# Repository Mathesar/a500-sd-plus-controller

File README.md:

# a500-sd-plus-controller
This is a dual micro-SD card plus Ethernet controller for the Amiga 500.
The controller piggybacks on the odd CIA (CIA A) chip on the Amiga 500 motherboard.

## Table of Contents
* [Micro-SD](#micro-sd)
* [Ethernet](#ethernet)
* [Drivers](#drivers)
* [Performance](#performance)
* [Pictures](#pictures)
* [Building](#building)

## Micro-SD
The two Micro-SD cards are operated in SPI mode.
Using the 68000 movep (move to/from peripheral) instruction and optimized code the driver reaches a raw throughput of up to 450kB/s on a standard 7MHz 68000 CPU. Due to device driver and filesystem overhead the overall speed is lower though.

The primary channel is intended for internal use. The micro-SD card in this slot functions as a fixed harddisk. The secondary channel is intended to be used with an extension cable to hold an external (hot-swappable if the driver supports it) micro-SD card. 
For this purpose, proper measures are taken to control signal integrity over the extension cable. The controller can also handle any current surges that can occur during hot swapping without overloading the Amiga power rail.

## Ethernet
The Ethernet controller is a Microchip ENC28J60 device. It is also connected over SPI and uses the INT2 interrupt. The ENC28J60 supports a 10Mbit network connection.
The interface is built in a slightly non-standard way to maximum immunity for external interference.

## Drivers
The Micro-SD cards are supported by [sd-lide.device](https://github.com/Mathesar/sd_lide.device).

The Ethernet controller is supported by [enc28j60.device](https://github.com/Mathesar/enc28j60.device).

## Performance
On a standard Amiga 500 with a 7MHz 68000 CPU running OS3.1 and AmiTCP 3.0b2 the following performance is reached:

* 250kB/s read speed for the Micro-SD cards as reported by SysInfo.
* Up to 22kB/s network download speed which is mostly limited by CPU speed.

Much better performance which is only limited by the speed of the E-clk (~600..700kB/s) can be expected when a faster CPU is installed.

## Pictures

Proof that this was actually built:

And the obligatory SysInfo screenshot:

## Building
Under [releases](https://github.com/Mathesar/a500-sd-plus-controller/releases) you will find the latest gerbers, bill of materials, bitstream, etc.
The files are in a format that is suitable for most well-known PCBA manufacturers.
I would recommend having the boards soldered professionally. This project uses small compononents and especially the CPLD is not solderable by hand. I had the boards made with all the SMD parts and the ethernet connector mounted. I only soldered the pinheaders and the CIA socket myself. For the pinheaders that plug into the CIA socket on the A500 motherboard, be sure to use the THIN and ROUND (aka "turned") pinheaders. Otherwise the motherboard socket WILL be damaged.

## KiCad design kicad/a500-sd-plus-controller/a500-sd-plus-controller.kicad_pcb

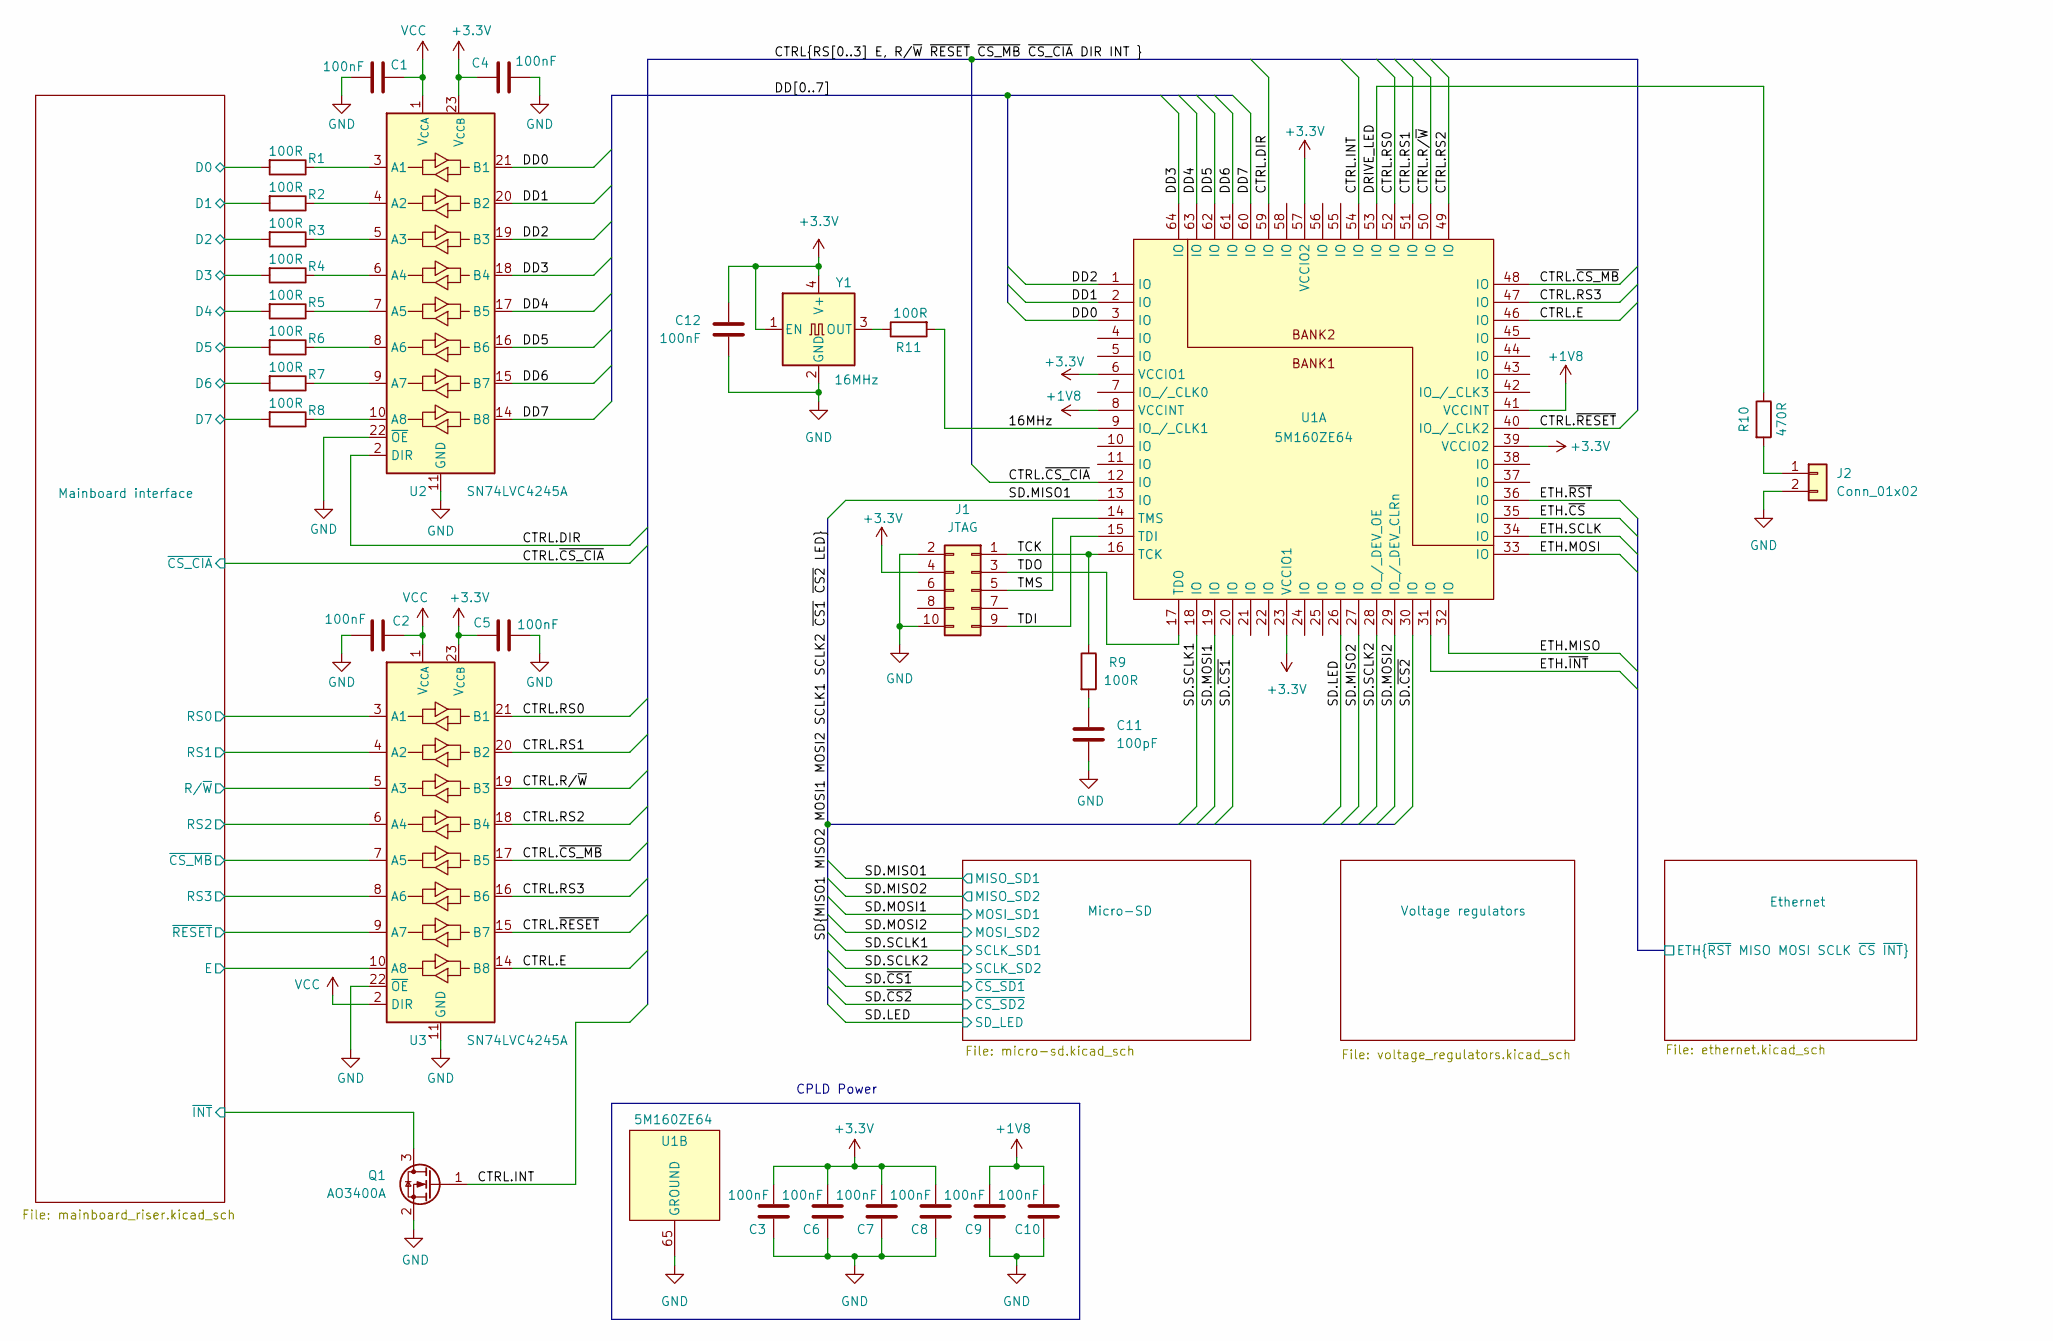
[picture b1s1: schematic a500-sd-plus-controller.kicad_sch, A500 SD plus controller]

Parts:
C1, C2, C3, C4, C5, C6, C7, C8, C9, C10, C12: 100nF; C_0603_1608Metric; LCSC Part # C14663
C11: 100pF; C_0603_1608Metric; LCSC Part # C14858
J1: JTAG; PinHeader_2x05_P2.54mm_Vertical
J2: Conn_01x02; PinHeader_1x02_P2.54mm_Vertical
Q1: AO3400A; SOT-23; MPN AO3400A; LCSC Part # C20917
R1, R2, R3, R4, R5, R6, R7, R8, R9, R11: 100R; R_0603_1608Metric; LCSC Part # C22775
R10: 470R; R_0603_1608Metric; LCSC Part # C23179
U1: 5M160ZE64; EQFP-64_7x7mm_P0.4mm; MPN 5M160ZE64C5N; LCSC Part # C431489
U2, U3: SN74LVC4245A; TSSOP-24_4.4x7.8mm_P0.65mm; MPN SN74LVC4245APWR; LCSC Part # C7859
Y1: 16MHz; Oscillator_SMD_SeikoEpson_SG210-4Pin_2.5x2.0mm; MPN X1G0041710027; LCSC Part # C255993

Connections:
+1V8: C9.1, C10.1, U1.8 (VCCINT), U1.41 (VCCINT); also elsewhere on the board
+3.3V: C3.1, C4.2, C5.2, C6.1, C7.1, C8.1, C12.2, J1.4, U1.6 (VCCIO1), U1.23 (VCCIO1), U1.39 (VCCIO2), U1.57 (VCCIO2), U2.23 (V_{CCB}), U2.24 (V_{CCB}), U3.23 (V_{CCB}), U3.24 (V_{CCB}), Y1.1 (EN), Y1.4 (V+); also elsewhere on the board
/16MHz: R11.2, U1.9 (IO_/_CLK1)
/CTRL.DIR: U1.59 (IO), U2.2 (DIR)
/CTRL.E: U1.46 (IO), U3.14 (B8)
/CTRL.INT: Q1.1 (G), U1.54 (IO)
/CTRL.RS0: U1.52 (IO), U3.21 (B1)
/CTRL.RS1: U1.51 (IO), U3.20 (B2)
/CTRL.RS2: U1.49 (IO), U3.18 (B4)
/CTRL.RS3: U1.47 (IO), U3.16 (B6)
/CTRL.R/~W: U1.50 (IO), U3.19 (B3)
/CTRL.~CS_CIA: U1.12 (IO); also elsewhere on the board
/CTRL.~CS_MB: U1.48 (IO), U3.17 (B5)
/CTRL.~RESET: U1.40 (IO_/_CLK2), U3.15 (B7)
/DD0: U1.3 (IO), U2.21 (B1)
/DD1: U1.2 (IO), U2.20 (B2)
/DD2: U1.1 (IO), U2.19 (B3)
/DD3: U1.64 (IO), U2.18 (B4)
/DD4: U1.63 (IO), U2.17 (B5)
/DD5: U1.62 (IO), U2.16 (B6)
/DD6: U1.61 (IO), U2.15 (B7)
/DD7: U1.60 (IO), U2.14 (B8)
/DRIVE_LED: R10.1, U1.53 (IO)
/Ethernet/ETH.MISO: U1.32 (IO); also elsewhere on the board
/Ethernet/ETH.MOSI: U1.33 (IO); also elsewhere on the board
/Ethernet/ETH.SCLK: U1.34 (IO); also elsewhere on the board
/Ethernet/ETH.~CS: U1.35 (IO); also elsewhere on the board
/Ethernet/ETH.~INT: U1.31 (IO); also elsewhere on the board
/Ethernet/ETH.~RST: U1.36 (IO); also elsewhere on the board
/Mainboard interface/D0: R1.2; also elsewhere on the board
/Mainboard interface/D1: R2.2; also elsewhere on the board
/Mainboard interface/D2: R3.2; also elsewhere on the board
/Mainboard interface/D3: R4.2; also elsewhere on the board
/Mainboard interface/D4: R5.2; also elsewhere on the board
/Mainboard interface/D5: R6.2; also elsewhere on the board
/Mainboard interface/D6: R7.2; also elsewhere on the board
/Mainboard interface/D7: R8.2; also elsewhere on the board
/Mainboard interface/E: U3.10 (A8); also elsewhere on the board
/Mainboard interface/RS0: U3.3 (A1); also elsewhere on the board
/Mainboard interface/RS1: U3.4 (A2); also elsewhere on the board
/Mainboard interface/RS2: U3.6 (A4); also elsewhere on the board
/Mainboard interface/RS3: U3.8 (A6); also elsewhere on the board
/Mainboard interface/R/~W: U3.5 (A3); also elsewhere on the board
/Mainboard interface/~CS_MB: U3.7 (A5); also elsewhere on the board
/Mainboard interface/~INT: Q1.3 (D); also elsewhere on the board
/Mainboard interface/~RESET: U3.9 (A7); also elsewhere on the board
/SD.LED: U1.26 (IO); also elsewhere on the board
/SD.MISO1: U1.13 (IO); also elsewhere on the board
/SD.MISO2: U1.27 (IO); also elsewhere on the board
/SD.MOSI1: U1.19 (IO); also elsewhere on the board
/SD.MOSI2: U1.29 (IO_/_DEV_CLRn); also elsewhere on the board
/SD.SCLK1: U1.18 (IO); also elsewhere on the board
/SD.SCLK2: U1.28 (IO_/_DEV_OE); also elsewhere on the board
/SD.~CS1: U1.20 (IO); also elsewhere on the board
/SD.~CS2: U1.30 (IO); also elsewhere on the board
/TCK: J1.1, R9.1, U1.16 (TCK)
/TDI: J1.9, U1.15 (TDI)
/TDO: J1.3, U1.17 (TDO)
/TMS: J1.5, U1.14 (TMS)
GND: C1.1, C2.1, C3.2, C4.1, C5.1, C6.2, C7.2, C8.2, C9.2, C10.2, C11.1, C12.1, J1.2, J1.10, J2.2, Q1.2 (S), U1.65 (GROUND), U2.11 (GND), U2.12 (GND), U2.13 (GND), U2.22 (~OE), U3.11 (GND), U3.12 (GND), U3.13 (GND), U3.22 (~OE), Y1.2 (GND); also elsewhere on the board
unnamed: C11.2, R9.2
unnamed: J2.1, R10.2
unnamed: R1.1, U2.3 (A1)
unnamed: R2.1, U2.4 (A2)
unnamed: R3.1, U2.5 (A3)
unnamed: R4.1, U2.6 (A4)
unnamed: R5.1, U2.7 (A5)
unnamed: R6.1, U2.8 (A6)
unnamed: R7.1, U2.9 (A7)
unnamed: R8.1, U2.10 (A8)
unnamed: R11.1, Y1.3 (OUT)
VCC: C1.2, C2.2, U2.1 (V_{CCA}), U3.1 (V_{CCA}), U3.2 (DIR); also elsewhere on the board

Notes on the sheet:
CPLD Power

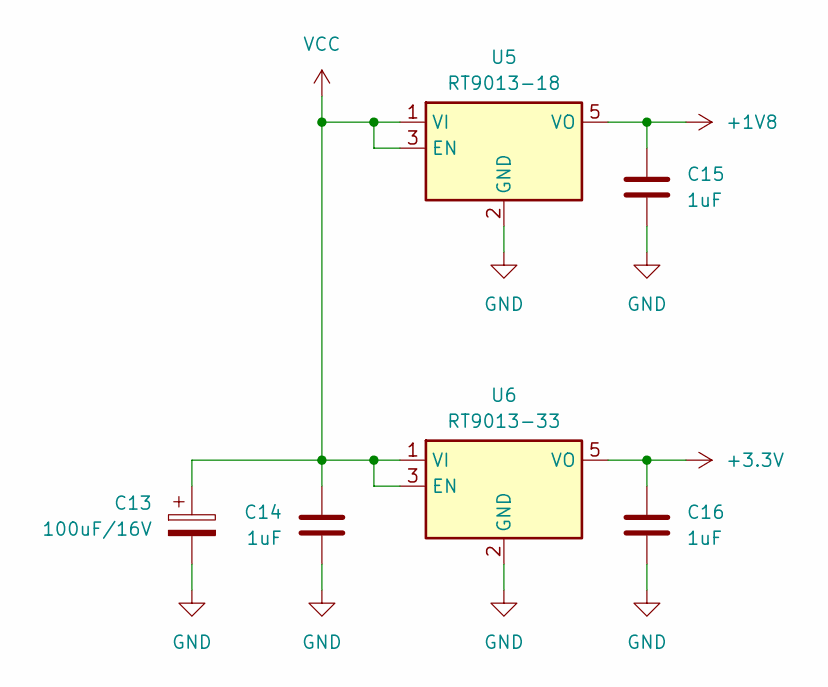
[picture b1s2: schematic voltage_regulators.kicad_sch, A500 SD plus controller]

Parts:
C13: 100uF/16V; CP_Radial_D8.0mm_P2.50mm; MPN EH71CM101E07OT; LCSC Part # C112487
C14, C15, C16: 1uF; C_0805_2012Metric; LCSC Part # C28323
U5: RT9013-18; SOT-23-5; MPN RT9013-18GB; LCSC Part # C22435116
U6: RT9013-33; SOT-23-5; MPN TPRT9013-33GB; LCSC Part # C587158

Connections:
+1V8: C15.2, U5.5 (VO); also elsewhere on the board
+3.3V: C16.2, U6.5 (VO); also elsewhere on the board
GND: C13.2, C14.1, C15.1, C16.1, U5.2 (GND), U6.2 (GND); also elsewhere on the board
VCC: C13.1, C14.2, U5.1 (VI), U5.3 (EN), U6.1 (VI), U6.3 (EN); also elsewhere on the board

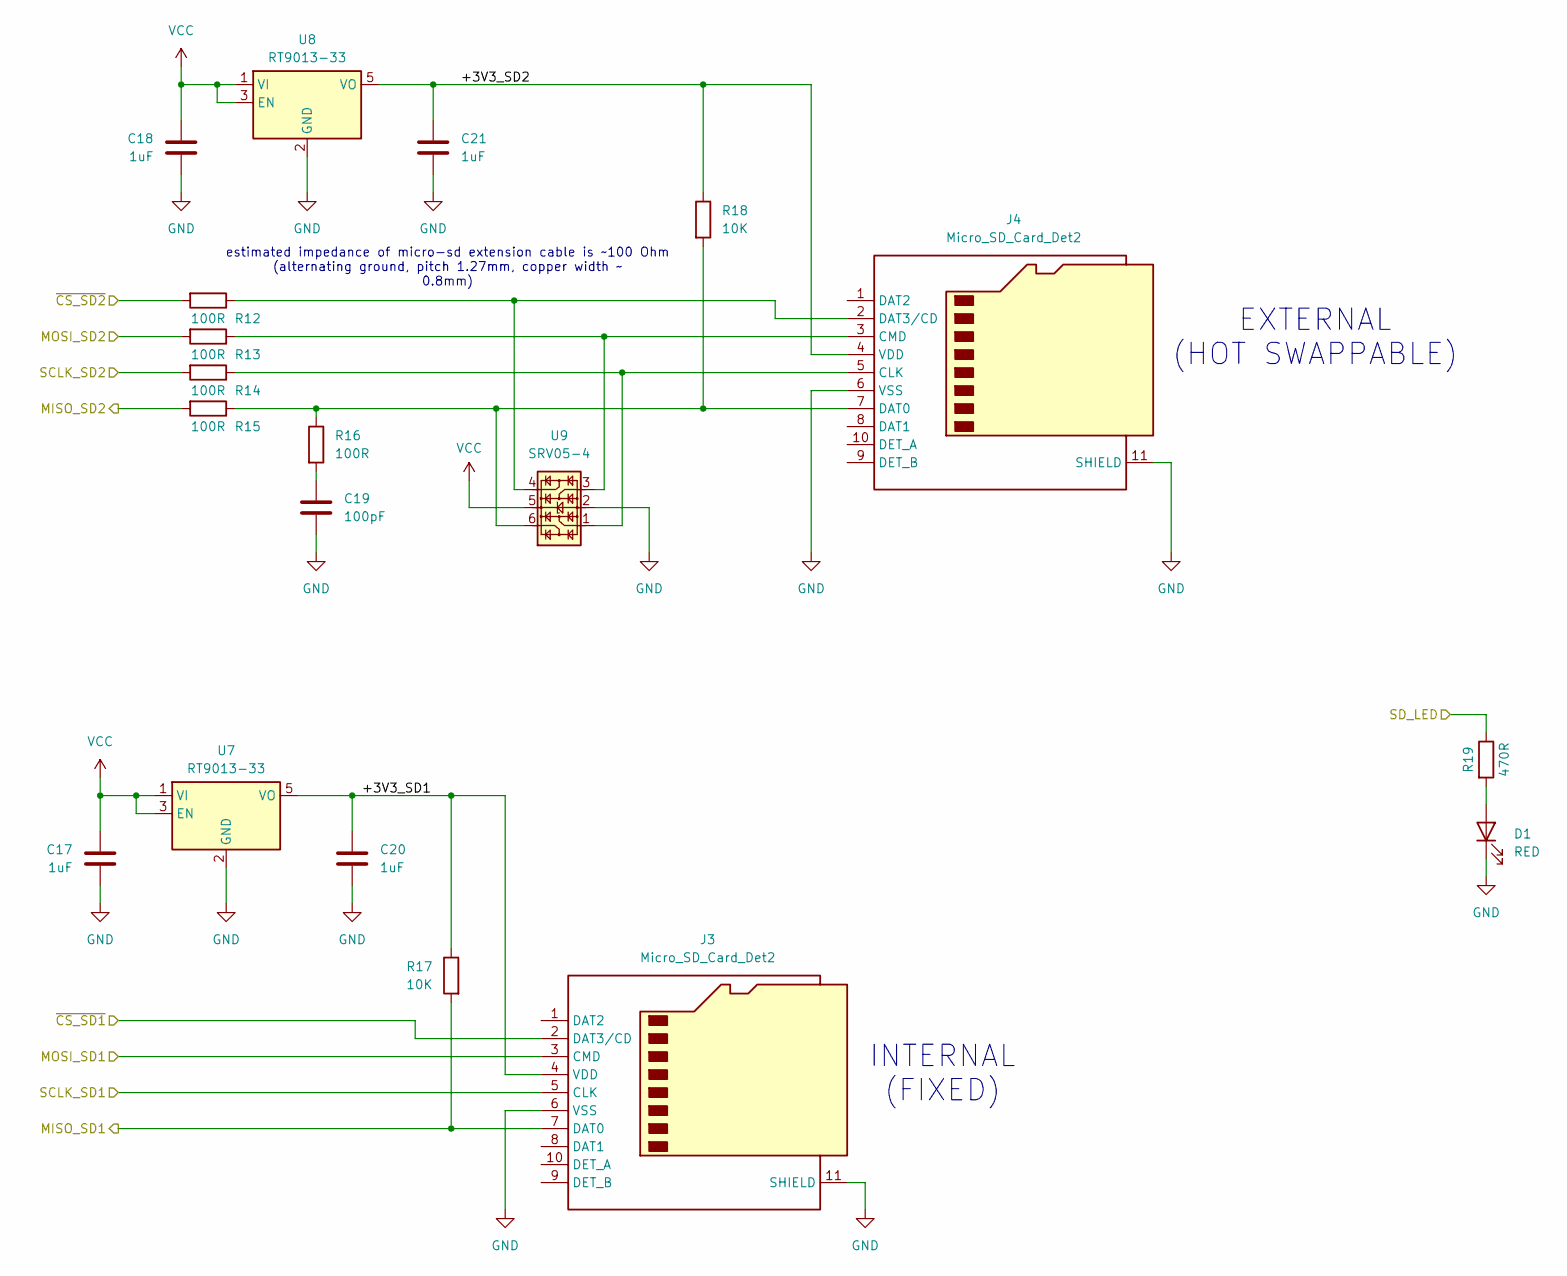
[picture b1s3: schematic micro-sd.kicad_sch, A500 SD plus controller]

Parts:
C17, C18, C20, C21: 1uF; C_0805_2012Metric; LCSC Part # C28323
C19: 100pF; C_0603_1608Metric; LCSC Part # C14858
D1: RED; LED_0805_2012Metric; MPN NCD0805R1; LCSC Part # C84256
J3, J4: Micro_SD_Card_Det2; microSD_HC_Hirose_DM3AT-SF-PEJM5; MPN DM3AT-SF-PEJM5; LCSC Part # C114218
R12, R13, R14, R15, R16: 100R; R_0603_1608Metric; LCSC Part # C22775
R17, R18: 10K; R_0603_1608Metric; LCSC Part # C25804
R19: 470R; R_0603_1608Metric; LCSC Part # C23179
U7, U8: RT9013-33; SOT-23-5; MPN TPRT9013-33GB; LCSC Part # C587158
U9: SRV05-4; SOT-23-6; MPN SRV05-4; LCSC Part # C2836319

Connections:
/Micro-SD/+3V3_SD1: C20.2, J3.4 (VDD), R17.1, U7.5 (VO)
/Micro-SD/+3V3_SD2: C21.2, J4.4 (VDD), R18.1, U8.5 (VO)
/SD.LED: R19.1; also elsewhere on the board
/SD.MISO1: J3.7 (DAT0), R17.2; also elsewhere on the board
/SD.MISO2: R15.2; also elsewhere on the board
/SD.MOSI1: J3.3 (CMD); also elsewhere on the board
/SD.MOSI2: R13.2; also elsewhere on the board
/SD.SCLK1: J3.5 (CLK); also elsewhere on the board
/SD.SCLK2: R14.2; also elsewhere on the board
/SD.~CS1: J3.2 (DAT3/CD); also elsewhere on the board
/SD.~CS2: R12.2; also elsewhere on the board
GND: C17.1, C18.1, C19.1, C20.1, C21.1, D1.1 (K), J3.6 (VSS), J3.11 (SHIELD), J4.6 (VSS), J4.11 (SHIELD), U7.2 (GND), U8.2 (GND), U9.2; also elsewhere on the board
unnamed: C19.2, R16.2
unnamed: D1.2 (A), R19.2
unnamed: J4.5 (CLK), R14.1, U9.1
unnamed: J4.3 (CMD), R13.1, U9.3
unnamed: J4.7 (DAT0), R15.1, R16.1, R18.2, U9.6
unnamed: J4.2 (DAT3/CD), R12.1, U9.4
VCC: C17.2, C18.2, U7.1 (VI), U7.3 (EN), U8.1 (VI), U8.3 (EN), U9.5; also elsewhere on the board

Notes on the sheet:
INTERNAL (FIXED)
EXTERNAL (HOT SWAPPABLE)
estimated impedance of micro-sd extension cable is ~100 Ohm (alternating ground, pitch 1.27mm, copper width ~ 0.8mm)

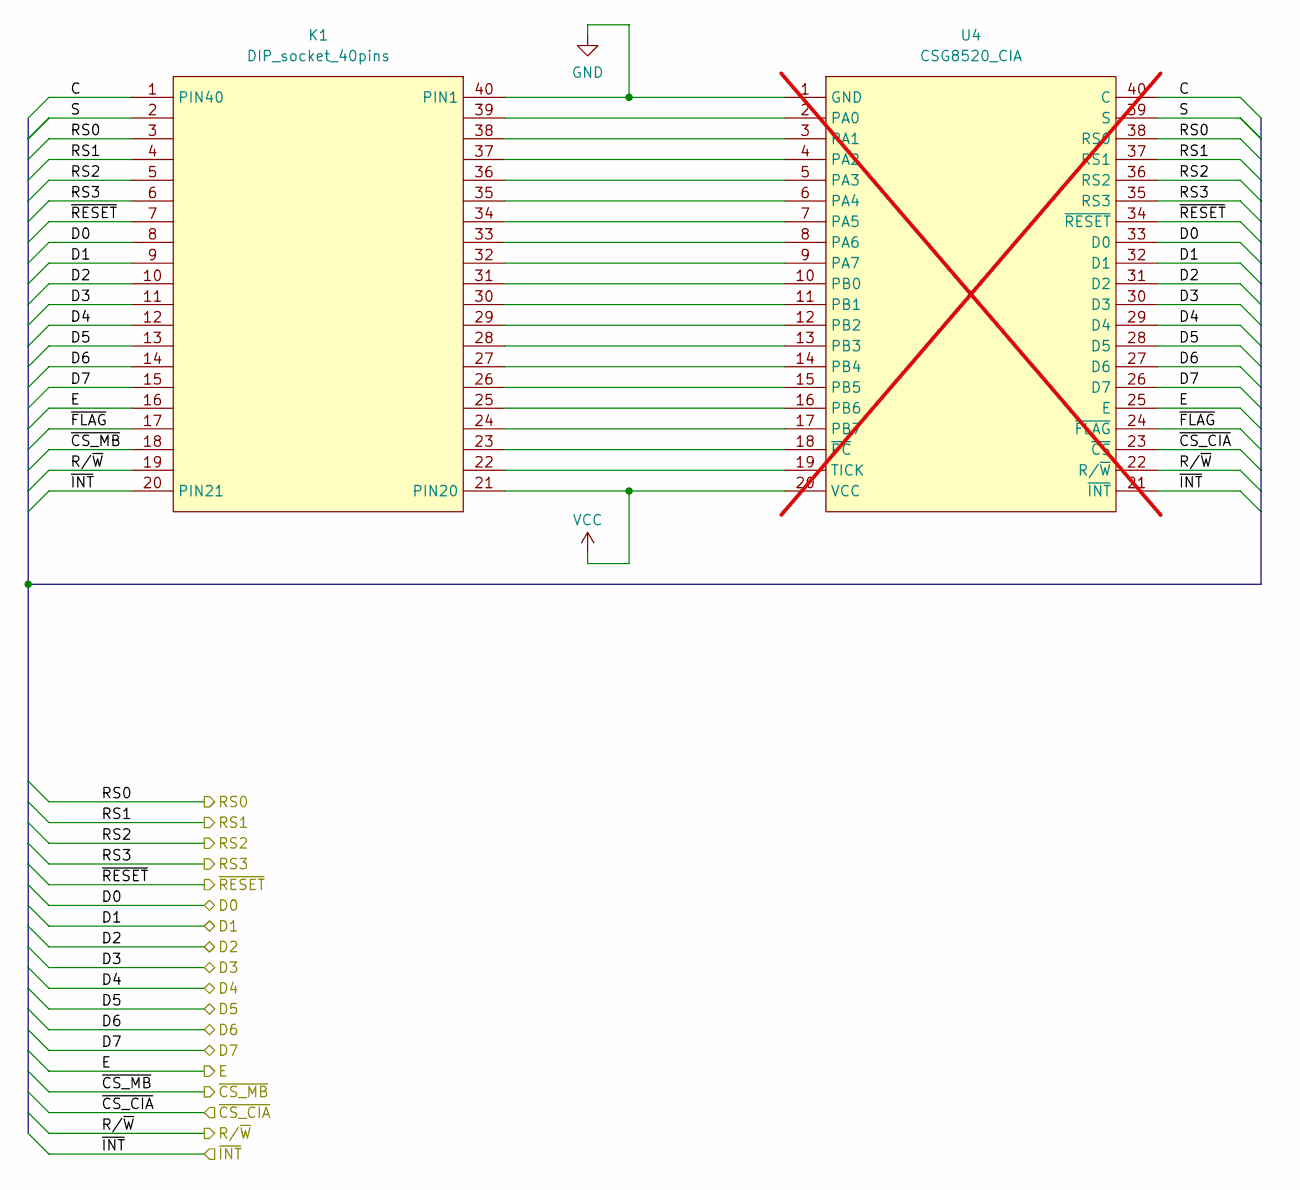
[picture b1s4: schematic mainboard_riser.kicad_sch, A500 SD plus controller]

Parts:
K1: DIP_socket_40pins; DIP-40_W15.24mm
U4: CSG8520_CIA; DIP-40_W15.24mm; not fitted

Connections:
/CTRL.~CS_CIA: U4.23 (~CS); also elsewhere on the board
/Mainboard interface/C: K1.1 (PIN40), U4.40 (C)
/Mainboard interface/D0: K1.8, U4.33 (D0); also elsewhere on the board
/Mainboard interface/D1: K1.9, U4.32 (D1); also elsewhere on the board
/Mainboard interface/D2: K1.10, U4.31 (D2); also elsewhere on the board
/Mainboard interface/D3: K1.11, U4.30 (D3); also elsewhere on the board
/Mainboard interface/D4: K1.12, U4.29 (D4); also elsewhere on the board
/Mainboard interface/D5: K1.13, U4.28 (D5); also elsewhere on the board
/Mainboard interface/D6: K1.14, U4.27 (D6); also elsewhere on the board
/Mainboard interface/D7: K1.15, U4.26 (D7); also elsewhere on the board
/Mainboard interface/E: K1.16, U4.25 (E); also elsewhere on the board
/Mainboard interface/RS0: K1.3, U4.38 (RS0); also elsewhere on the board
/Mainboard interface/RS1: K1.4, U4.37 (RS1); also elsewhere on the board
/Mainboard interface/RS2: K1.5, U4.36 (RS2); also elsewhere on the board
/Mainboard interface/RS3: K1.6, U4.35 (RS3); also elsewhere on the board
/Mainboard interface/R/~W: K1.19, U4.22 (R/~W); also elsewhere on the board
/Mainboard interface/S: K1.2, U4.39 (S)
/Mainboard interface/~CS_MB: K1.18; also elsewhere on the board
/Mainboard interface/~FLAG: K1.17, U4.24 (~FLAG)
/Mainboard interface/~INT: K1.20 (PIN21), U4.21 (~INT); also elsewhere on the board
/Mainboard interface/~RESET: K1.7, U4.34 (~RESET); also elsewhere on the board
GND: K1.40 (PIN1), U4.1 (GND); also elsewhere on the board
unnamed: K1.39, U4.2 (PA0)
unnamed: K1.38, U4.3 (PA1)
unnamed: K1.37, U4.4 (PA2)
unnamed: K1.36, U4.5 (PA3)
unnamed: K1.35, U4.6 (PA4)
unnamed: K1.34, U4.7 (PA5)
unnamed: K1.33, U4.8 (PA6)
unnamed: K1.32, U4.9 (PA7)
unnamed: K1.31, U4.10 (PB0)
unnamed: K1.30, U4.11 (PB1)
unnamed: K1.29, U4.12 (PB2)
unnamed: K1.28, U4.13 (PB3)
unnamed: K1.27, U4.14 (PB4)
unnamed: K1.26, U4.15 (PB5)
unnamed: K1.25, U4.16 (PB6)
unnamed: K1.24, U4.17 (PB7)
unnamed: K1.22, U4.19 (TICK)
unnamed: K1.23, U4.18 (~PC)
VCC: K1.21 (PIN20), U4.20 (VCC); also elsewhere on the board

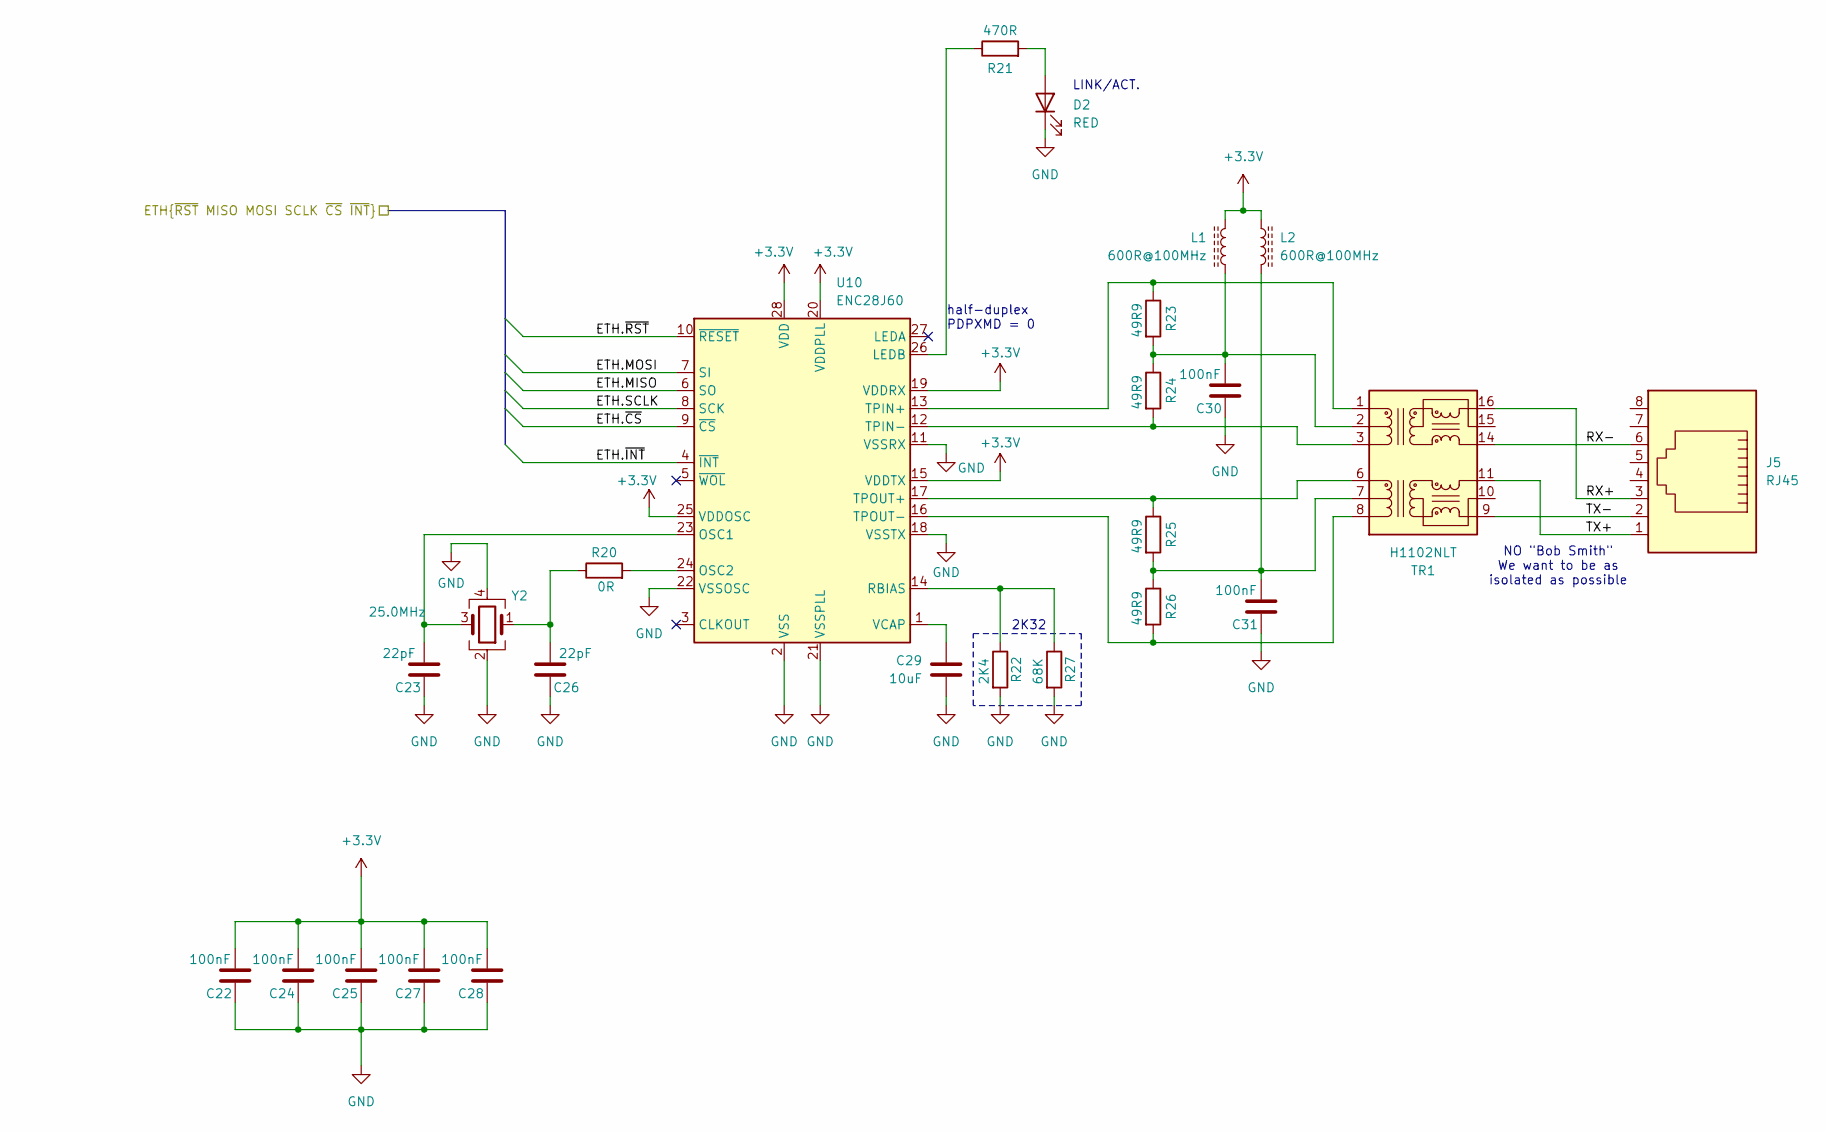
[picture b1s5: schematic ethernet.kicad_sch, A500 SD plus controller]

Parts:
C22, C24, C25, C27, C28, C30, C31: 100nF; C_0603_1608Metric; LCSC Part # C14663
C23, C26: 22pF; C_0603_1608Metric; LCSC Part # C1653
C29: 10uF; C_0805_2012Metric; LCSC Part # C15850
D2: RED; LED_0805_2012Metric; MPN NCD0805R1; LCSC Part # C84256
J5: RJ45; R-RJ45R08P-A004; MPN R-RJ45R08P-A004; LCSC Part # C385834
L1, L2: 600R@100MHz; L_0805_2012Metric; MPN GZ2012D601TF; LCSC Part # C1017
R20: 0R; R_0603_1608Metric; LCSC Part # C21189
R21: 470R; R_0603_1608Metric; LCSC Part # C23179
R22: 2K4; R_0603_1608Metric; LCSC Part # C22940
R23, R24, R25, R26: 49R9; R_0603_1608Metric; LCSC Part # C23185
R27: 68K; R_0603_1608Metric; LCSC Part # C23231
TR1: H1102NLT; Transformer_Ethernet_Bourns_PT61017PEL; MPN H1102NLT; LCSC Part # C18584
U10: ENC28J60; SSOP-28_5.3x10.2mm_P0.65mm; MPN ENC28J60-I/SS; LCSC Part # C411626
Y2: 25.0MHz; Crystal_SMD_SeikoEpson_FA238V-4Pin_3.2x2.5mm; MPN X322525MOB4SI; LCSC Part # C9006

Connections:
+3.3V: C22.1, C24.1, C25.1, C27.1, C28.1, L1.1, L2.1, U10.15 (VDDTX), U10.19 (VDDRX), U10.20 (VDDPLL), U10.25 (VDDOSC), U10.28 (VDD); also elsewhere on the board
/Ethernet/ETH.MISO: U10.6 (SO); also elsewhere on the board
/Ethernet/ETH.MOSI: U10.7 (SI); also elsewhere on the board
/Ethernet/ETH.SCLK: U10.8 (SCK); also elsewhere on the board
/Ethernet/ETH.~CS: U10.9 (~CS); also elsewhere on the board
/Ethernet/ETH.~INT: U10.4 (~INT); also elsewhere on the board
/Ethernet/ETH.~RST: U10.10 (~RESET); also elsewhere on the board
/Ethernet/RX+: J5.3, TR1.16 (TX+)
/Ethernet/RX-: J5.6, TR1.14 (TX-)
/Ethernet/TX+: J5.1, TR1.11 (RX+)
/Ethernet/TX-: J5.2, TR1.9 (RX-)
GND: C22.2, C23.2, C24.2, C25.2, C26.2, C27.2, C28.2, C29.1, C30.2, C31.2, D2.1 (K), R22.2, R27.2, U10.2 (VSS), U10.11 (VSSRX), U10.18 (VSSTX), U10.21 (VSSPLL), U10.22 (VSSOSC), Y2.2, Y2.4; also elsewhere on the board
unnamed: C26.1, R20.1, Y2.1
unnamed: D2.2 (A), R21.2
unnamed: C31.1, L2.2, R25.2, R26.1, TR1.7 (C_RD)
unnamed: C30.1, L1.2, R23.2, R24.1, TR1.2 (C_TD)
unnamed: R25.1, TR1.6 (RD+), U10.17 (TPOUT+)
unnamed: R26.2, TR1.8 (RD-), U10.16 (TPOUT-)
unnamed: R23.1, TR1.1 (TD+), U10.13 (TPIN+)
unnamed: R24.2, TR1.3 (TD-), U10.12 (TPIN-)
unnamed: R21.1, U10.26 (LEDB)
unnamed: C23.1, U10.23 (OSC1), Y2.3
unnamed: R20.2, U10.24 (OSC2)
unnamed: R22.1, R27.1, U10.14 (RBIAS)
unnamed: C29.2, U10.1 (VCAP)

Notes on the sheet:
LINK/ACT.
NO "Bob Smith" We want to be as isolated as possible
2K32
half-duplex PDPXMD = 0

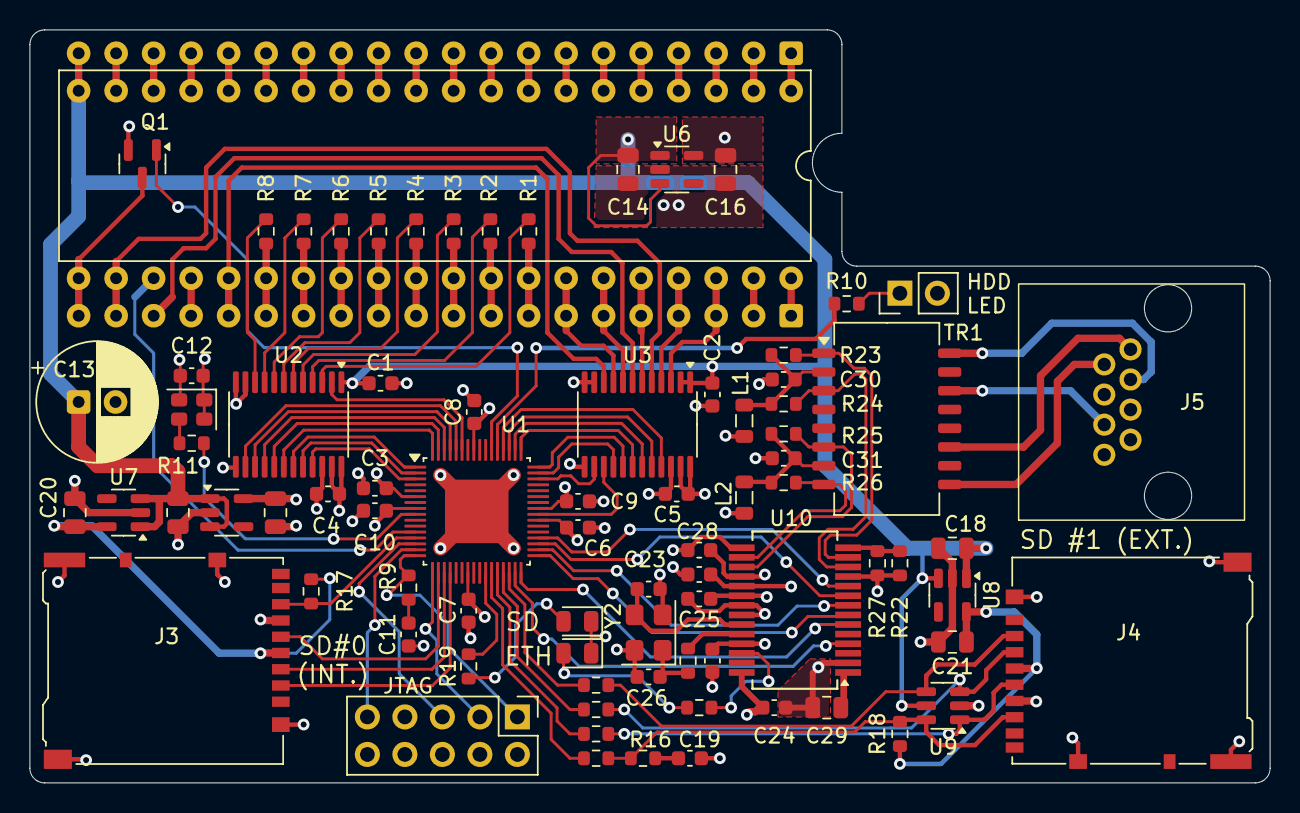
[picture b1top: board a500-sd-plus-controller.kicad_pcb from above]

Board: 4 copper layers, 84.0 x 51.0 mm, 82 parts (1 on the bottom side), 118 nets.

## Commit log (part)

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2025-08-21 first setup with multiple speed 8bit shifter
2025-08-31 added test benches, fixed bugs. work in progress
2025-09-05 new register map
    documentation update
2025-09-06 added CRC16 computation in hardware
2025-09-11 Shifter optimized a bit
    Added CRC read registers
    Updated testbench
    Updated README
2025-09-12 added explicit global buffers for Altera MAX5 target
2025-09-19 passing testbench, 68K bus is now handled asynchronously from
    synchronous core SPI logic
2025-09-20 renamed some nets
    updated comments
2025-09-21 - shifter is now clocked at double the frequency to simplify logic
    - fixed MOSI glitch at end of byte transfer
    - reduced waitstate between transfers to 0.5 clock cycle average
    - SCLK and MOSI now come directly from flipflips without any combinatorial logic inbetween for cleaner timing
2025-09-29 started work on hardware
2025-10-01 Work in progress, this version piggybacks on the unused CIA register 0xb
2025-10-03 fixed some bugs
    rewrote testbench
2025-10-04 saved a few LE's as these are not needed when interfacing to the E clock interface.
2025-10-18 more work done on hardware
    basic schematic done
    layout in progress
2025-10-19 added add ethernet controller
    still work in progress
2025-10-21 routing completely done
    todo: review footprints and cleanup silkscreen
2025-10-22 cleaned up silkscreen and 3D models
2025-10-25 PCB done, this version has been sent to fabrication
2025-10-26 fixed a bug where async r/w signal was used in statemachine
    external bus driver is now enabled before internal driver to avoid clashes
    code cleanup
2025-10-26 added .bak files to gitignore
2025-10-26 added documentation
2025-11-02 moved busy flag to highest bit so that driver code can use
    68K "tst.b (a1)" instruction and branch on negative flag
2025-11-09 fixed polarity of SD/HDD LEDs
2025-12-03 minor change of cycle logic
2025-12-04 added interrupt controller to enable/disable interrupt
2025-12-06 updated documentation
2025-12-19 Added Quartus project
2025-12-19 added pictures to README
2025-12-19 fixed image links
2025-12-19 fixed links again
2025-12-19 added schematics
2025-12-19 Added links to drivers.
2026-01-10 updated readme with building hints

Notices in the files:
kicad/a500-sd-plus-controller/a500-sd-plus-controller.kicad_pcb:
CERN-OHL-S V2.0
